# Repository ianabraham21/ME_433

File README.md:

# Mini Segway Code
source code for a mini segway project for advanced mechatronics

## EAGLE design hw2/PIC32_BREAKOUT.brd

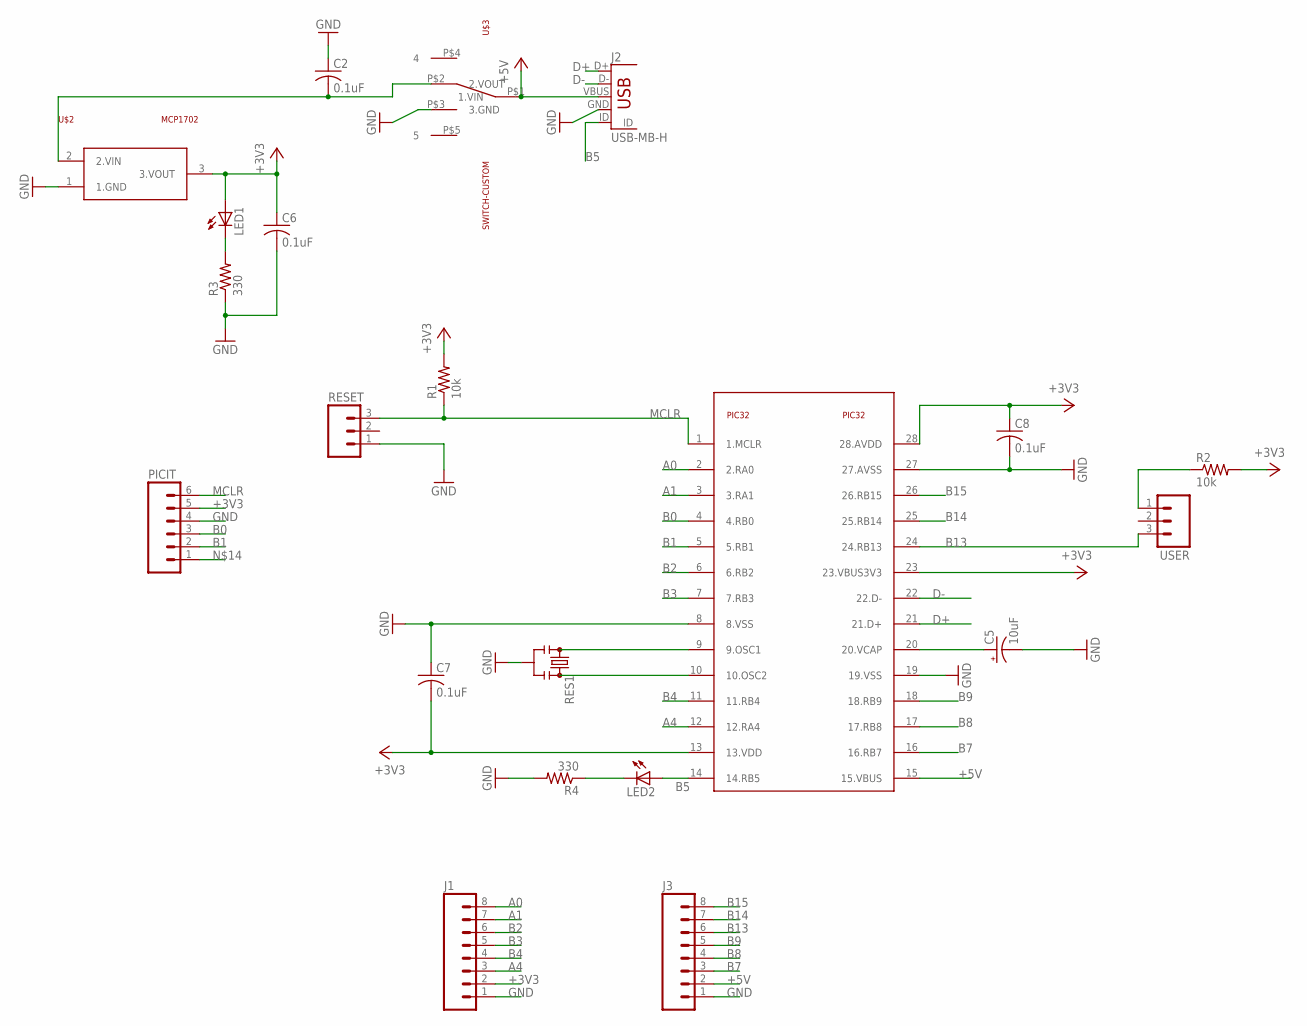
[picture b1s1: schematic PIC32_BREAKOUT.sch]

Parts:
C2, C6, C7, C8: 0.1uF; C025-024X044
C5: 10uF; B45181A
J1, J3: M08; 1X08_ROUND
J2: USB-MB-H
LED1, LED2: LED3MM
PIC32: PIC32; DIL28-3
PICIT: M06SILK_FEMALE_PTH; 1X06
R1, R2: 10k; 0204/7
R3, R4: 330; 0204/7
RES1: RESONATORPTH; RESONATOR-PTH
RESET: M03LOCK; 1X03_LOCK
U$2: MCP1702; TO92
U$3: SWITCH-CUSTOM; SWITCH-CUS-H1
USER: M03LOCK; 1X03_LOCK

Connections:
+3V3: C6.1, C7.2, C8.1, J1.2, LED1.A, PIC32.13 (13.VDD), PIC32.23 (23.VBUS3V3), PIC32.28 (28.AVDD), PICIT.5, R1.2, R2.2, U$2.3 (3.VOUT)
+5V: J2.VBUS, J3.2, PIC32.15 (15.VBUS), U$3.P$1 (1.VIN)
A0: J1.8, PIC32.2 (2.RA0)
A1: J1.7, PIC32.3 (3.RA1)
A4: J1.3, PIC32.12 (12.RA4)
B0: PIC32.4 (4.RB0), PICIT.3
B1: PIC32.5 (5.RB1), PICIT.2
B2: J1.6, PIC32.6 (6.RB2)
B3: J1.5, PIC32.7 (7.RB3)
B4: J1.4, PIC32.11 (11.RB4)
B5: J2.ID, LED2.A, PIC32.14 (14.RB5)
B7: J3.3, PIC32.16 (16.RB7)
B8: J3.4, PIC32.17 (17.RB8)
B9: J3.5, PIC32.18 (18.RB9)
B13: J3.6, PIC32.24 (24.RB13), USER.3
B14: J3.7, PIC32.25 (25.RB14)
B15: J3.8, PIC32.26 (26.RB15)
D+: J2.D+, PIC32.21 (21.D+)
D-: J2.D-, PIC32.22 (22.D-)
GND: C2.1, C5.-, C6.2, C7.1, C8.2, J1.1, J2.GND, J3.1, PIC32.8 (8.VSS), PIC32.19 (19.VSS), PIC32.27 (27.AVSS), PICIT.4, R3.1, R4.2, RES1.2, RESET.1, U$2.1 (1.GND), U$3.P$3 (3.GND)
MCLR: PIC32.1 (1.MCLR), PICIT.6, R1.1, RESET.3
unnamed: C5.+, PIC32.20 (20.VCAP)
unnamed: C2.2, U$2.2 (2.VIN), U$3.P$2 (2.VOUT)
unnamed: LED1.K (C), R3.2
unnamed: LED2.K (C), R4.1
unnamed: PIC32.9 (9.OSC1), RES1.1
unnamed: PIC32.10 (10.OSC2), RES1.3
unnamed: R2.1, USER.1

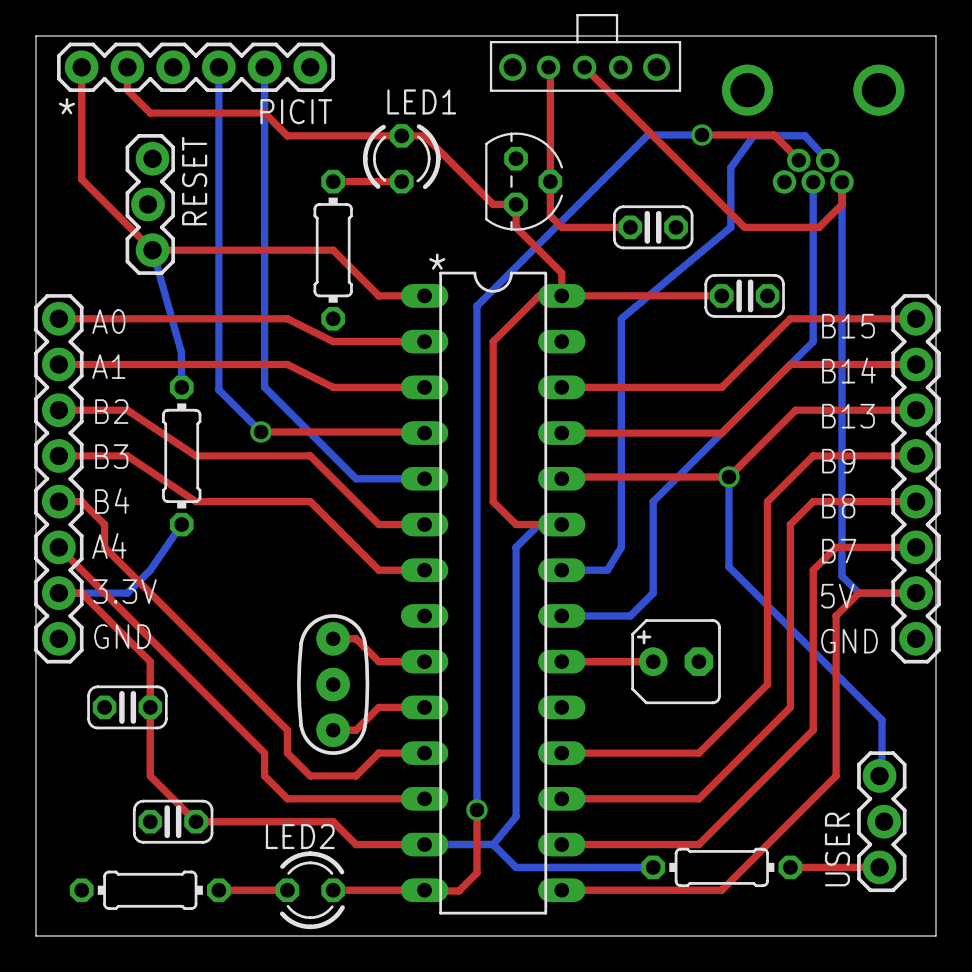
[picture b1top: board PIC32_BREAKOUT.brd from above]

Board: 2 copper layers, 50.0 x 50.0 mm, 21 parts (0 on the bottom side), 28 nets.

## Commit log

2016-03-31 added class notes
2016-04-03 new xc32 files
2016-04-04 working code
2016-04-04 Pictures
2016-04-14 Ready to Check
2016-04-14 changed file name
2016-04-14 Ready to Print
2016-04-14 clean up
2016-04-21 Finalized spi comm with DAC
2016-04-21 scope images
2016-04-21 Added the I2C capabilities
2016-04-26 Added better i2c library
2016-04-27 added some functions
2016-05-06 got LCD to work
2016-05-06 Now got the IMU + LCD working
2016-05-10 Uploaded most recent updates
2016-06-01 started the segway balance code
2016-06-04 got the segway working
2016-06-04 pic cdc
2016-06-08 moved all the files from android studio
2017-12-28 cleaned up the files
2017-12-28 okay
2017-12-28 added more readme info

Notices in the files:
parts and their libraries:
SparkFun-FreqCtrl: Licensing: Creative Commons ShareAlike 4.0 International - https://creativecommons.org/licenses/by-sa/4.0
